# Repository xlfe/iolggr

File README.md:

### iolggr - log all the things

This repo contains:
 
* the [LUA](https://github.com/xlfe/iolggr/tree/master/lua_firmware)
 code that runs on [nodemcu-firmware](https://github.com/nodemcu/nodemcu-firmware)
* the [hardware](https://github.com/xlfe/iolggr/tree/master/hardware) KiCad files for the device and 
 [schematic](https://github.com/xlfe/iolggr/blob/master/hardware/schematic.pdf?raw=true)
* the EmberJS [frontend](https://github.com/xlfe/iolggr/tree/master/frontend) that is the client-side of [iolggr.appspot.com](http://iolggr.appspot.com)
* the Google App Engine [backend](https://github.com/xlfe/iolggr/tree/master/iolggr) that runs the above site

You may also be interested in:

* PCBs manufactured through [dirtyPCBs](http://dirtypcbs.com/view.php?share=3451&accesskey=3c95e6f53910fa1181111da9e7cac7ba).
* My [BMP280 firmware for nodemcu/ESP8266](https://github.com/xlfe/nodemcu-firmware)
* [spiffy](https://github.com/xlfe/spiffy) - a (dirty-hack!) spiffs modification to bundle multiple (lua) files into a ROM to burn to the ESP8266 in one shot
* [Photos from the build](http://www.smugmug.com/gallery/n-mLQfL/i-7JtGxx4)

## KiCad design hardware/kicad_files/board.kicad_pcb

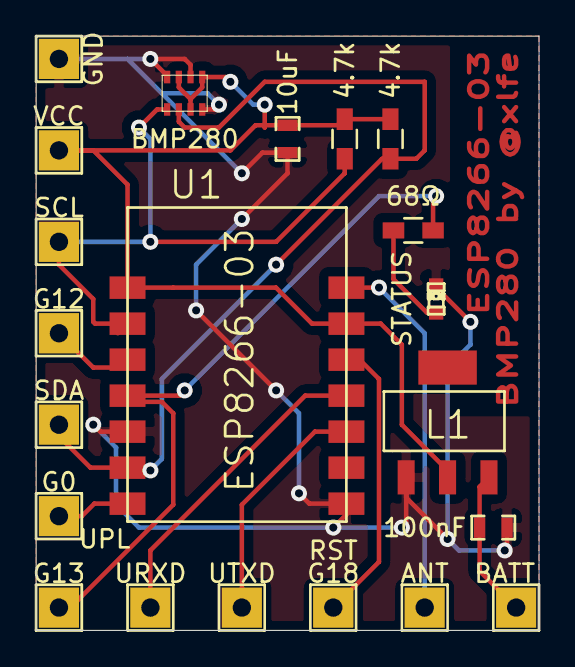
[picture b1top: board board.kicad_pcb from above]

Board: 2 copper layers, 27.9 x 33.0 mm, 21 parts (0 on the bottom side), 13 nets.

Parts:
ANT: ANT; Socket_Strip_Straight_1x01
BATT: BATT; Socket_Strip_Straight_1x01
C1: 100nF; SMD-0603_c
C2: 10uF; SMD-0603_c
D0: STATUS; LED-0603
G0: G0 UPL; Socket_Strip_Straight_1x01
G12: G12; Socket_Strip_Straight_1x01
G13: G13; Socket_Strip_Straight_1x01
G18: G18 RST; Socket_Strip_Straight_1x01
GND: GND; Socket_Strip_Straight_1x01
L1: LD1117S33CTR; SOT-223
R1, R2: 4.7k; R_0603_HandSoldering
R3: 68Ω; R_0603_HandSoldering
SCL: SCL; Socket_Strip_Straight_1x01
SDA: SDA; Socket_Strip_Straight_1x01
U1: ESP8266-03
U2: BMP280
URXD: URXD; Socket_Strip_Straight_1x01
UTXD: UTXD; Socket_Strip_Straight_1x01
VCC: CONN_VCC; Socket_Strip_Straight_1x01

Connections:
/BATT: BATT.1, C1.1, L1.3
/GND: C1.2, C2.2, D0.2, GND.1, L1.1, U1.1, U1.12, U2.1, U2.5, U2.7
/URXD: U1.4, URXD.1
/UTXD: U1.3, UTXD.1
unnamed: D0.1, R3.1
unnamed: G18.1, U1.5
unnamed: G12.1, U1.10
unnamed: G13.1, R3.2, U1.11
unnamed: G0.1, U1.14
unnamed: ANT.1, U1.7
SCL: R1.2, SCL.1, U1.9, U2.4
SDA: R2.2, SDA.1, U1.13, U2.3
VCC: C2.1, L1.2, R1.1, R2.1, U1.6, U1.8, U2.2, U2.6, U2.8, VCC.1

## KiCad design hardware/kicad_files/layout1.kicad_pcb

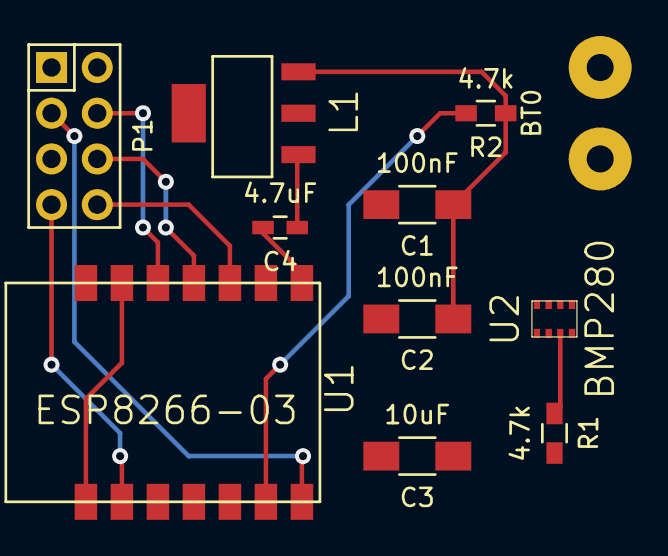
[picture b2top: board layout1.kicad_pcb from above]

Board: 2 copper layers, 11 parts (0 on the bottom side), 9 nets.

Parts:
BT0: BATTERY; SolderWirePad_2x_1-5mmDrill
C1, C2: 100nF; C_1206_HandSoldering
C3: 10uF; C_1206_HandSoldering
C4: 4.7uF; C_0603_HandSoldering
L1: MCP1825; SOT-223
P1: CONN_02X04; Pin_Header_Straight_2x04
R1, R2: 4.7k; R_0603_HandSoldering
U1: ESP8266-03
U2: BMP280

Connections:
GPIO0: P1.3, U1.14
unnamed: BT0.1, C4.1, L1.1
unnamed: C1.2, C2.2, C3.2, C4.2, U1.1, U1.12, U2.1, U2.5, U2.7
unnamed: C1.1, C2.1, C3.1, L1.3, R1.1, R2.1, U1.6, U1.8, U2.2
RST: P1.4, U1.5
SCL: P1.7, R1.2, U1.9, U2.4
SDA: P1.5, R2.2, U1.13, U2.3
URXD: P1.6, U1.4
UTXD: P1.8, U1.3

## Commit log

2015-01-15 Initial Commit from Ember CLI v0.1.7
    ,,,,,,,,,,,,,,,,,,,,,,,,,,,,,,,,,,,,,,,,,,,....,,........,.. . . .,...........,
    ,,,,,,,,,,,,,,,:...,,.,,,,,,,,,,,,,,,,,,,,,.,,.,,......... .~.::::. ..........,
    ,,,,,,,,,,,,. .. .. .. ..,... ,+7ZOOOZ7=, . .,..... ~.=:::::: ..........,
    ,,,,,,,,,, .====IIIIISZ. .. 7ZSIIIIIIIIIIIIIII7ZO... .::..+:::::::= ..........,
    ,,,,,,,,, .=~:~~:~==IIIIII7ZIIIIIIIIIIIIIIIIIIIIIIISZ:....+::::::::, ..........,
    ,,,,,,,,, :::~~~~~~~==77ZIIIIIIIIIIIIIIIIIIIIIIIIIII7O..=~:::::::~............,
2015-01-18 Added app engine files
2015-01-18 Added lua firmware files
2015-01-18 Added hardware files to repo
2015-01-20 many updates - including working from auto urls
2015-01-20 Fixes #1
2015-01-22 Update firmware - seems to work well
2015-02-02 Add rollup capability
2015-02-05 Rollup refined, bssid dropped, name-mac-ip based resolution
2015-02-05 Lots of updates - moving to chart-device views
2015-02-06 Paging based on relative week or start-end dates or most recent observation
2015-02-06 Two lines on the same chart...
2015-02-09 rollup seperate, compressed formats for client
2015-02-09 Log micro offsets
2015-02-10 Multi charts working
2015-02-18 Fix start time
2015-02-19 Dont use Mode anymore
2015-02-19 iolggr BETA
2015-02-19 Label generation
2015-02-21 Better loading states, errors now show new setup page, added time period limits
2015-02-21 Fix bug in rollup - chunks didnt include previous data, also json dict keys are strings...
2015-02-21 Slice working, needed to convert dates back to native format from offset
2015-02-21 Speedups - no need to slice, lets try removing logging too
2015-03-05 Add a readme
2015-03-05 Add link to spiffy
2015-12-30 better asserts
2015-12-30 fix for no device
2017-02-04 refactor
2017-02-04 add receiver, include dofile(wifi.lua) in init.lua
2017-02-14 simplifying
2017-02-14 add rssi
2017-02-15 rollup and logging working
2017-06-14 first go at Om Next and Vega working to render the example
2017-06-18 need index.html
2017-06-18 added sass
2017-06-19 ignore sass cache
2017-06-25 start working with material design
2017-06-27 material-ui react componets working
2017-07-02 try google chart library
2017-07-04 global vs local state...
2018-01-03 add csv endpoint to show in google sheets
2018-01-21 add modified files
